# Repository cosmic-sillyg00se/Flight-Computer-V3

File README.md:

# Flight-Computer-V3
My very very first attempt at making an active control flight computer! It went horribly (as expected). Also really really ugly

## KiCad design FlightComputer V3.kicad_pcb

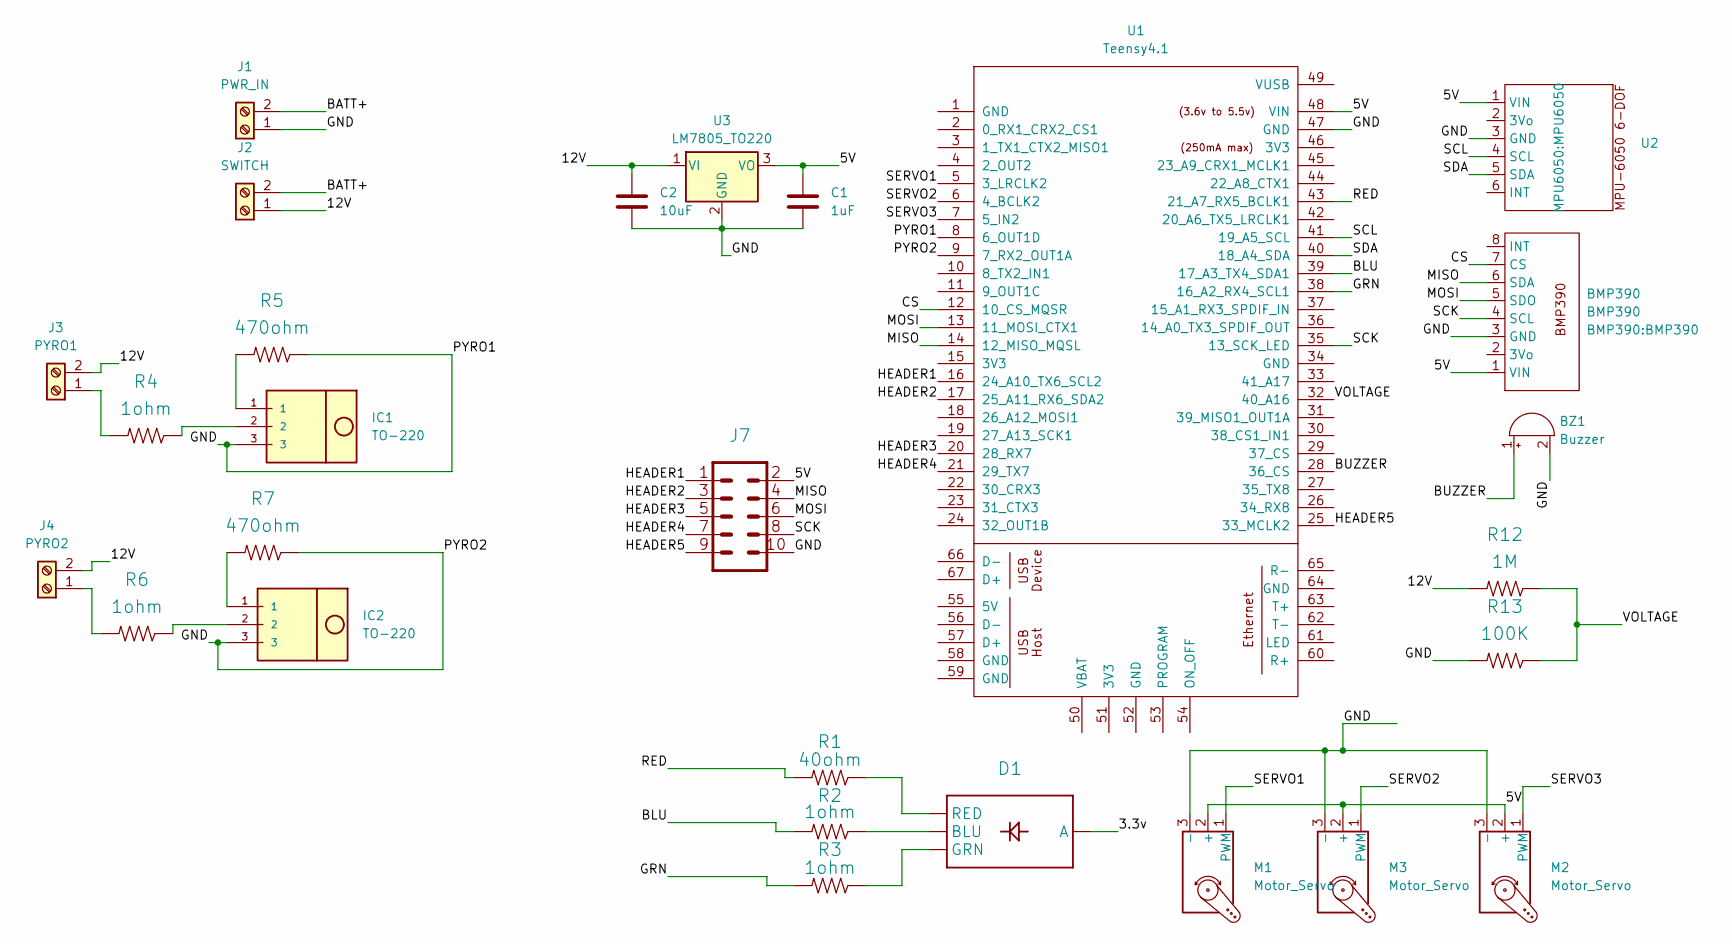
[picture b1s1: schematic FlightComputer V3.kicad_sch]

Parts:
BMP390: BMP390
BZ1: Buzzer; Buzzer_TDK_PS1240P02BT_D12.2mm_H6.5mm
C1: 1uF; C_Radial_D6.3mm_H5.0mm_P2.50mm
C2: 10uF; C_Radial_D6.3mm_H5.0mm_P2.50mm
D1: LED_D5.0mm-4_RGB_Staggered_Pins
IC1, IC2: TO-220; TO-220-3_Vertical
J1: PWR_IN; TerminalBlock_MaiXu_MX126-5.0-02P_1x02_P5.00mm
J2: SWITCH; TerminalBlock_MaiXu_MX126-5.0-02P_1x02_P5.00mm
J3: PYRO1; TerminalBlock_MaiXu_MX126-5.0-02P_1x02_P5.00mm
J4: PYRO2; TerminalBlock_MaiXu_MX126-5.0-02P_1x02_P5.00mm
J7: PinHeader_2x05_P2.54mm_Vertical
M1, M2, M3: Motor_Servo; PinHeader_1x03_P2.54mm_Vertical
R1: 40ohm; R_Axial_DIN0207_L6.3mm_D2.5mm_P7.62mm_Horizontal
R2, R3, R4, R6: 1ohm; R_Axial_DIN0207_L6.3mm_D2.5mm_P7.62mm_Horizontal
R5, R7: 470ohm; R_Axial_DIN0207_L6.3mm_D2.5mm_P7.62mm_Horizontal
R12: 1M; R_Axial_DIN0207_L6.3mm_D2.5mm_P7.62mm_Horizontal
R13: 100K; R_Axial_DIN0207_L6.3mm_D2.5mm_P7.62mm_Horizontal
U1: Teensy4.1; Teensy41
U2: MPU6050
U3: LM7805_TO220; TO-220-3_Vertical

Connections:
/3.3v: D1.2 (A)
/5V: BMP390.1 (VIN), C1.1, J7.2, M1.2 (+), M2.2 (+), M3.2 (+), U1.48 (VIN), U2.1 (VIN), U3.3 (VO)
/12V: C2.1, J2.1, J3.2, J4.2, R12.2, U3.1 (VI)
/BATT+: J1.2, J2.2
/BLU: R2.2, U1.39 (17_A3_TX4_SDA1)
/BUZZER: BZ1.1 (+), U1.28 (36_CS)
/CS: BMP390.7 (CS), U1.12 (10_CS_MQSR)
/GND: BMP390.3 (GND), BZ1.2 (-), C1.2, C2.2, IC1.3, IC2.3, J1.1, J7.10, M1.3 (-), M2.3 (-), M3.3 (-), R5.1, R7.1, R13.2, U1.8 (6_OUT1D), U1.9 (7_RX2_OUT1A), U1.47 (GND), U2.3 (GND), U3.2 (GND)
/GRN: R3.2, U1.38 (16_A2_RX4_SCL1)
/HEADER1: J7.1, U1.16 (24_A10_TX6_SCL2)
/HEADER2: J7.3, U1.17 (25_A11_RX6_SDA2)
/HEADER3: J7.5, U1.20 (28_RX7)
/HEADER4: J7.7, U1.21 (29_TX7)
/HEADER5: J7.9, U1.25 (33_MCLK2)
/MISO: BMP390.6 (SDA), J7.4, U1.14 (12_MISO_MQSL)
/MOSI: BMP390.5 (SDO), J7.6, U1.13 (11_MOSI_CTX1)
/PYRO3: U1.10 (8_TX2_IN1)
/PYRO4: U1.11 (9_OUT1C)
/RED: R1.2, U1.43 (21_A7_RX5_BCLK1)
/SCK: BMP390.4 (SCL), J7.8, U1.35 (13_SCK_LED)
/SCL: U1.41 (19_A5_SCL), U2.4 (SCL)
/SDA: U1.40 (18_A4_SDA), U2.5 (SDA)
/SERVO1: M1.1 (PWM), U1.5 (3_LRCLK2)
/SERVO2: M3.1 (PWM), U1.6 (4_BCLK2)
/SERVO3: M2.1 (PWM), U1.7 (5_IN2)
/VOLTAGE: R12.1, R13.1, U1.32 (40_A16)
unnamed: D1.4 (BLU), R2.1
unnamed: D1.3 (GRN), R3.1
unnamed: D1.1 (RED), R1.1
unnamed: IC1.1, R5.2
unnamed: IC1.2, R4.1
unnamed: IC2.1, R7.2
unnamed: IC2.2, R6.1
unnamed: J3.1, R4.2
unnamed: J4.1, R6.2

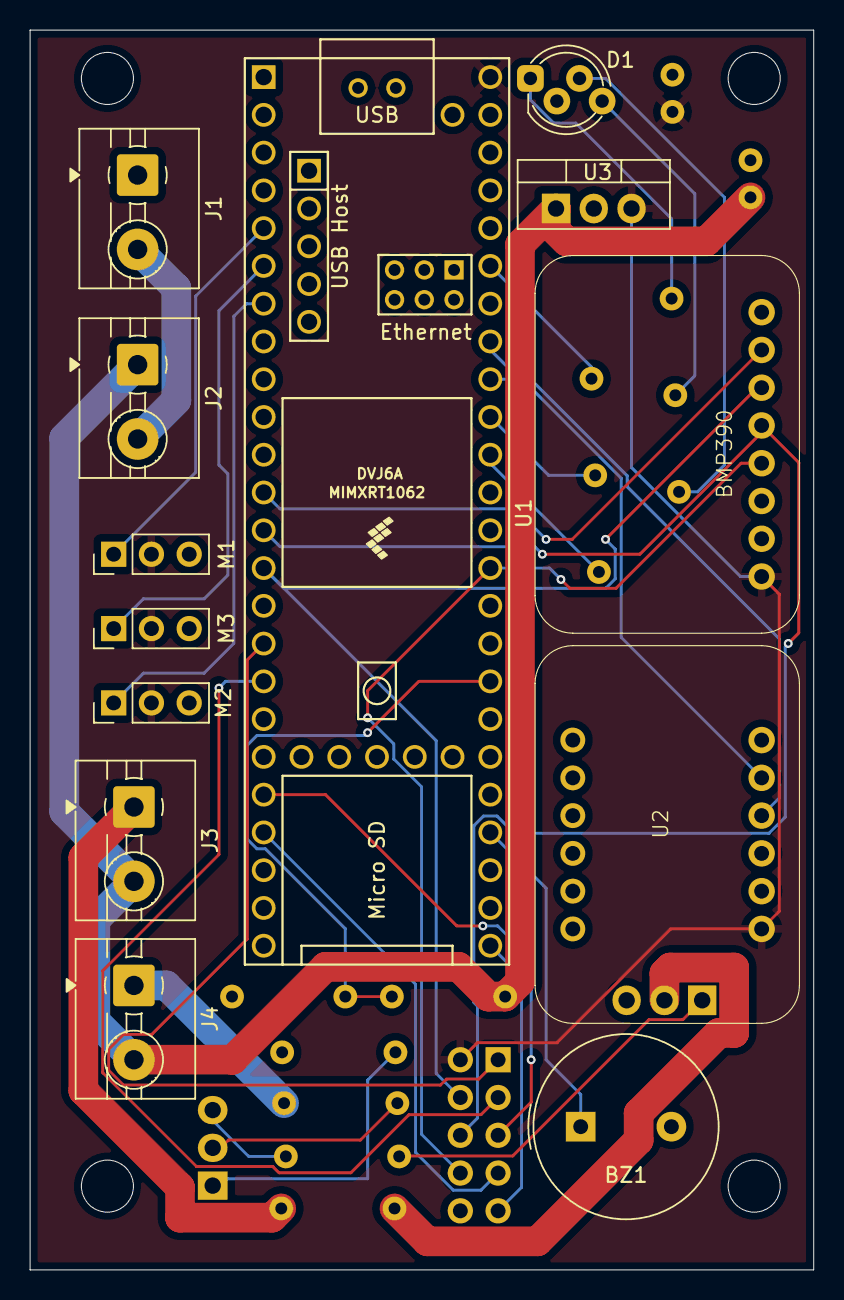
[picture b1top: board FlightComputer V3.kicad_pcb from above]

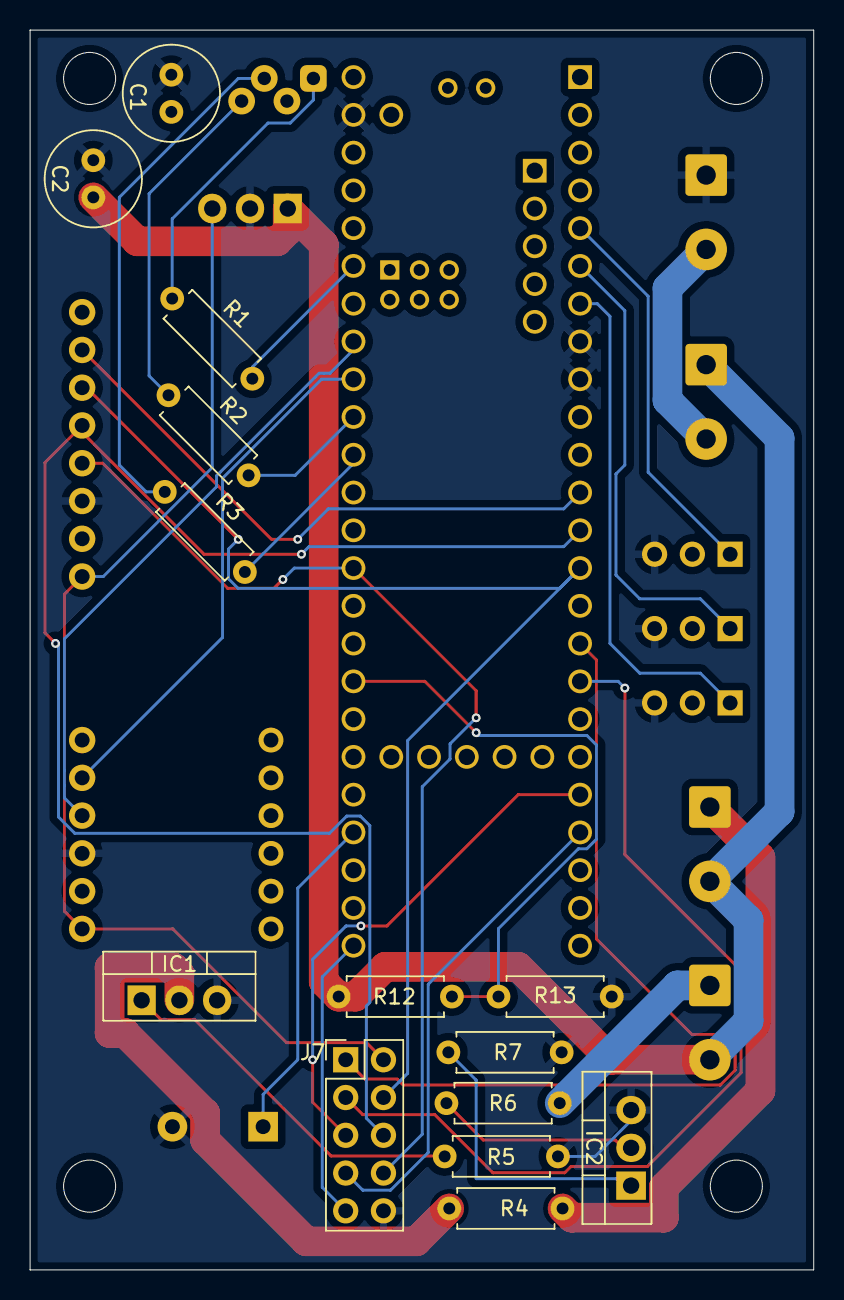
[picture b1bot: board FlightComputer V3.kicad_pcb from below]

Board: 2 copper layers, 52.7 x 83.4 mm, 27 parts (14 on the bottom side), 32 nets.

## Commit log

2026-02-05 Added all KiCad files
